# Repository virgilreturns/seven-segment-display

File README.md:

# seven-segment-display

# Description:
Embedded Microcontroller NUCELO-F401RE Multi-Digit Seven Segment LED Driver using Master-Transmit Only SPI communication with 74HC595 Shift Register.

The objectives of this project are to gain experience with configuring 32-bit microcontrollers, coding in C using the STMCubeIDE, learning how to use Git, using kicad to design footprints and PCBs, 
learning how to get the PCBs manufactured, and learning how to order correct components for cheap. 

This project spanned two months to complete. The code is open-source and free to use. 

# Signal Processing Flow Chart:

# Final Circuit Design

# Final PCB Design

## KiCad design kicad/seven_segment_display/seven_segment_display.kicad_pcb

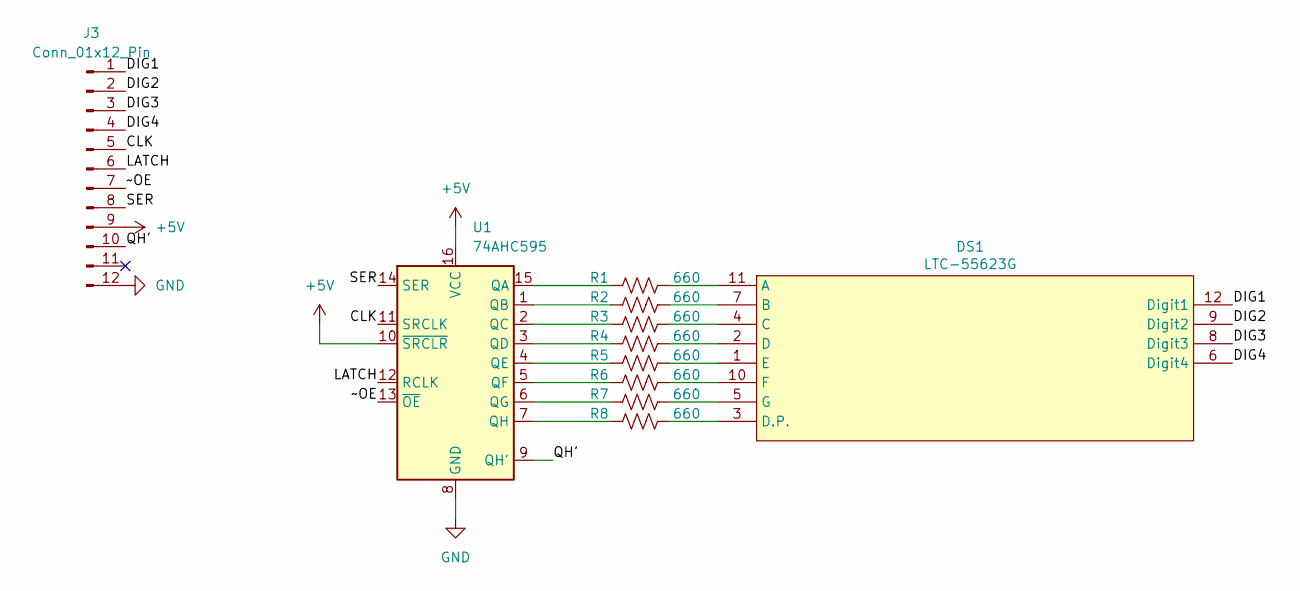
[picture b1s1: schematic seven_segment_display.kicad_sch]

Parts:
DS1: LTC-55623G; LTC_5623G-SDIP
J3: Conn_01x12_Pin; PinHeader_1x12_P2.54mm_Vertical
R1, R2, R3, R4, R5, R6, R7, R8: 660; R_Axial_DIN0207_L6.3mm_D2.5mm_P7.62mm_Horizontal
U1: 74AHC595; DIP-16_W7.62mm_Socket

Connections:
+5V: J3.9, U1.10 (~SRCLR), U1.16 (VCC)
/CLK: J3.5, U1.11 (SRCLK)
/DIG1: DS1.12 (Digit1), J3.1
/DIG2: DS1.9 (Digit2), J3.2
/DIG3: DS1.8 (Digit3), J3.3
/DIG4: DS1.6 (Digit4), J3.4
/LATCH: J3.6, U1.12 (RCLK)
/QH': J3.10, U1.9 (QH')
/SER: J3.8, U1.14 (SER)
/~OE: J3.7, U1.13 (~OE)
GND: J3.12, U1.8 (GND)
unnamed: DS1.11 (A), R1.2
unnamed: DS1.7 (B), R2.2
unnamed: DS1.4 (C), R3.2
unnamed: DS1.2 (D), R4.2
unnamed: DS1.3 (D.P.), R8.2
unnamed: DS1.1 (E), R5.2
unnamed: DS1.10 (F), R6.2
unnamed: DS1.5 (G), R7.2
unnamed: R1.1, U1.15 (QA)
unnamed: R2.1, U1.1 (QB)
unnamed: R3.1, U1.2 (QC)
unnamed: R4.1, U1.3 (QD)
unnamed: R5.1, U1.4 (QE)
unnamed: R6.1, U1.5 (QF)
unnamed: R7.1, U1.6 (QG)
unnamed: R8.1, U1.7 (QH)

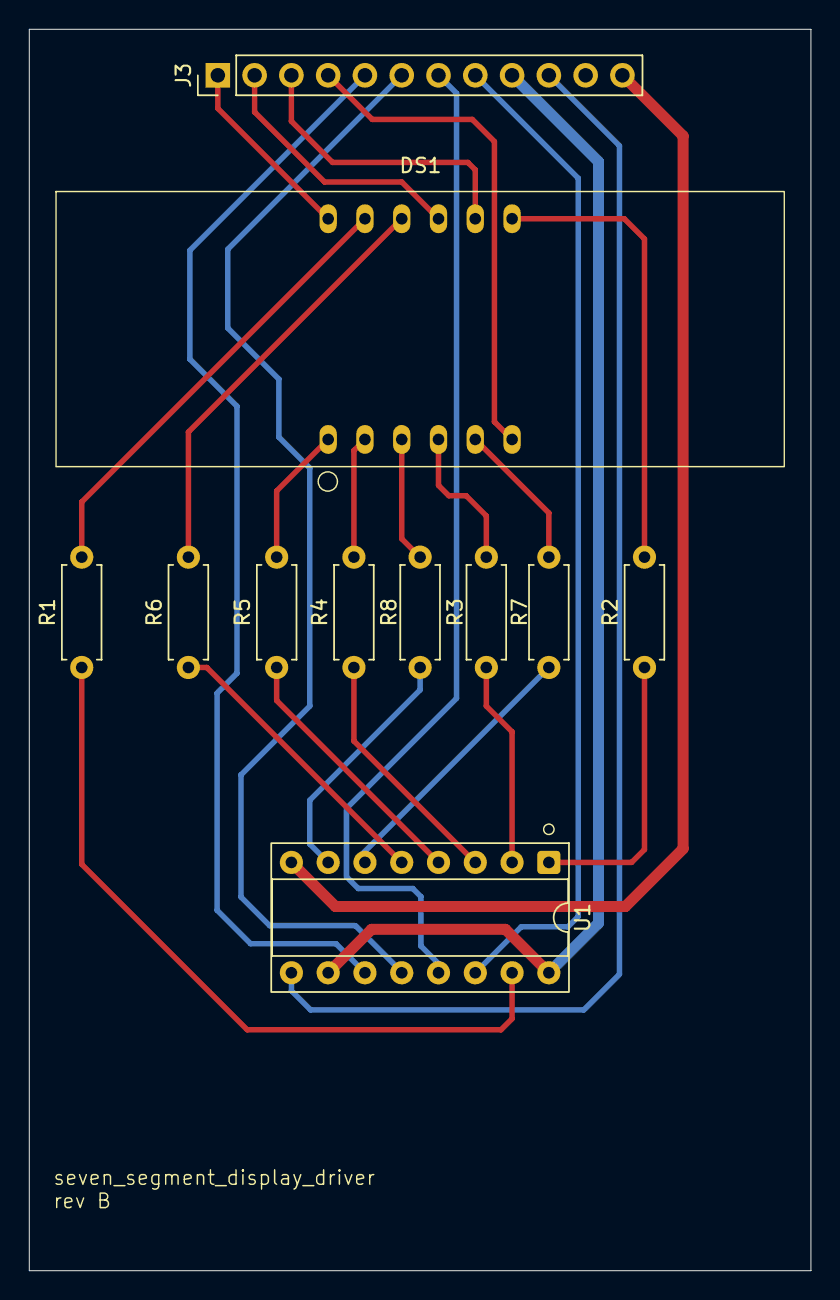
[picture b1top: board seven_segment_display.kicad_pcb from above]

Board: 2 copper layers, 54.0 x 85.7 mm, 11 parts (0 on the bottom side), 27 nets.

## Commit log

2025-04-21 successful updates
2025-04-21 pre adding debounce system
2025-04-21 debounce system implemented using interrupts processed in task 1 by main
2025-04-22 declare app_main
2025-04-24 Fixed re-declaring GPIO_PIN_ARRAY, successful test of multiplexing
2025-04-24 Migrate documentation
2025-04-25 It is complete
2025-04-25 documentation
2025-04-28 Scrolling feature introduced, data_buf and data_window members, algorithm for edit/play state machine
2025-05-01 Exti Line works, tested with onboard led
2025-05-01 timer3 isr running
2025-05-15 bug fixes in exti, hopefully finished UI implementation, requires integrated testing
2025-05-15 scrolling implemented testing required
2025-06-07 zapppp
2025-06-07 added kicad
2025-06-09 final pcb design completed
2025-06-18 ANDE RSON

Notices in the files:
kicad/seven_segment_display/seven_segment_display.kicad_pcb:
License: CC BY 4.0
